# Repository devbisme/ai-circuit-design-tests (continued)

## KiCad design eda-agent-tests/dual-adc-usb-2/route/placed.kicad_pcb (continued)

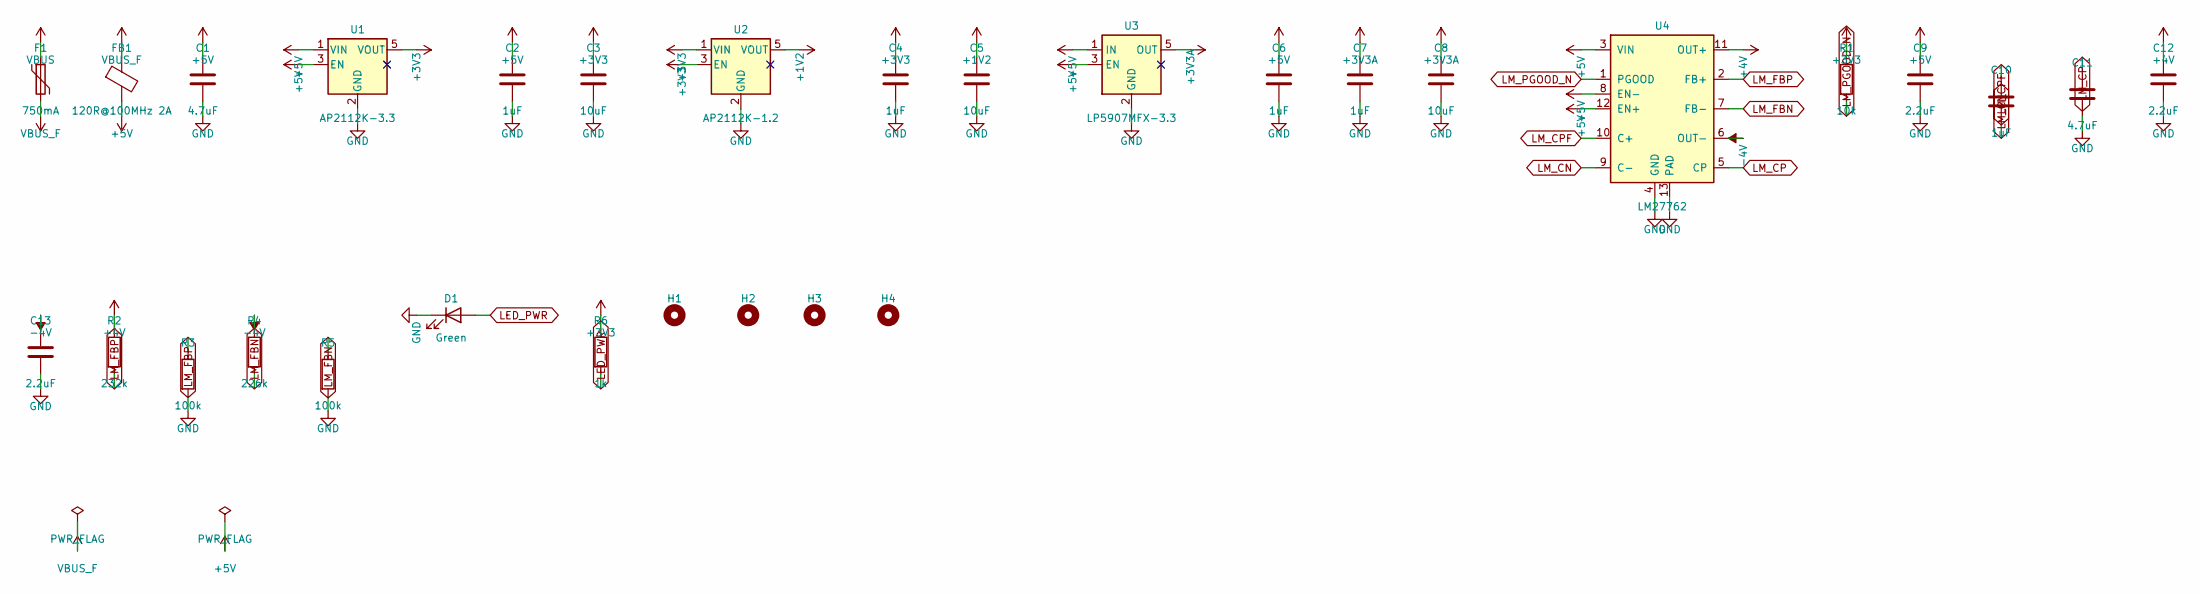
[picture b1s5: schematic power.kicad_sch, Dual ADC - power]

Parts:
C1, C11: 4.7uF; C_0805_2012Metric
C2, C4, C6, C7: 1uF; C_0603_1608Metric
C3, C5, C8: 10uF; C_0805_2012Metric
C9, C12, C13: 2.2uF; C_0805_2012Metric
C10: 1uF; C_0402_1005Metric
D1: Green; LED_0603_1608Metric
F1: 750mA; Fuse_1206_3216Metric; MPN 0ZCJ0050AF2E
FB1: 120R@100MHz 2A; L_0603_1608Metric; MPN BLM18AG601SN1D
H1, H2, H3, H4: MountingHole; MountingHole_3.2mm_M3
R1: 10k; R_0603_1608Metric
R2: 232k; R_0603_1608Metric
R3, R5: 100k; R_0603_1608Metric
R4: 226k; R_0603_1608Metric
R6: 1k; R_0603_1608Metric
U1: AP2112K-3.3; SOT-23-5; MPN AP2112K-3.3TRG1
U2: AP2112K-1.2; SOT-23-5; MPN AP2112K-1.2TRG1
U3: LP5907MFX-3.3; SOT-23-5; MPN LP5907MFX-3.3/NOPB
U4: LM27762; WSON-12-1EP_3x2mm_P0.5mm_EP1x2.65; MPN LM27762DSSR

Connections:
+1V2: C5.1, U2.5 (VOUT); also elsewhere on the board
+3V3A: C7.1, C8.1, U3.5 (OUT); also elsewhere on the board
+4V: C12.1, R2.1, U4.11 (OUT+); also elsewhere on the board
+5V: C1.1, C2.1, C6.1, C9.1, FB1.2, U1.1 (VIN), U1.3 (EN), U3.1 (IN), U3.3 (EN), U4.3 (VIN), U4.8 (EN-), U4.12 (EN+)
-4V: C13.1, R4.1, U4.6 (OUT-); also elsewhere on the board
LED_PWR: D1.2 (A), R6.2
LM_CN: C10.2, U4.9 (C-)
LM_CP: C11.1, U4.5 (CP)
LM_CPF: C10.1, U4.10 (C+)
LM_FBN: R4.2, R5.1, U4.7 (FB-)
LM_FBP: R2.2, R3.1, U4.2 (FB+)
LM_PGOOD_N: R1.2, U4.1 (PGOOD); also elsewhere on the board
VBUS: F1.1; also elsewhere on the board
VBUS_F: F1.2, FB1.1; also elsewhere on the board

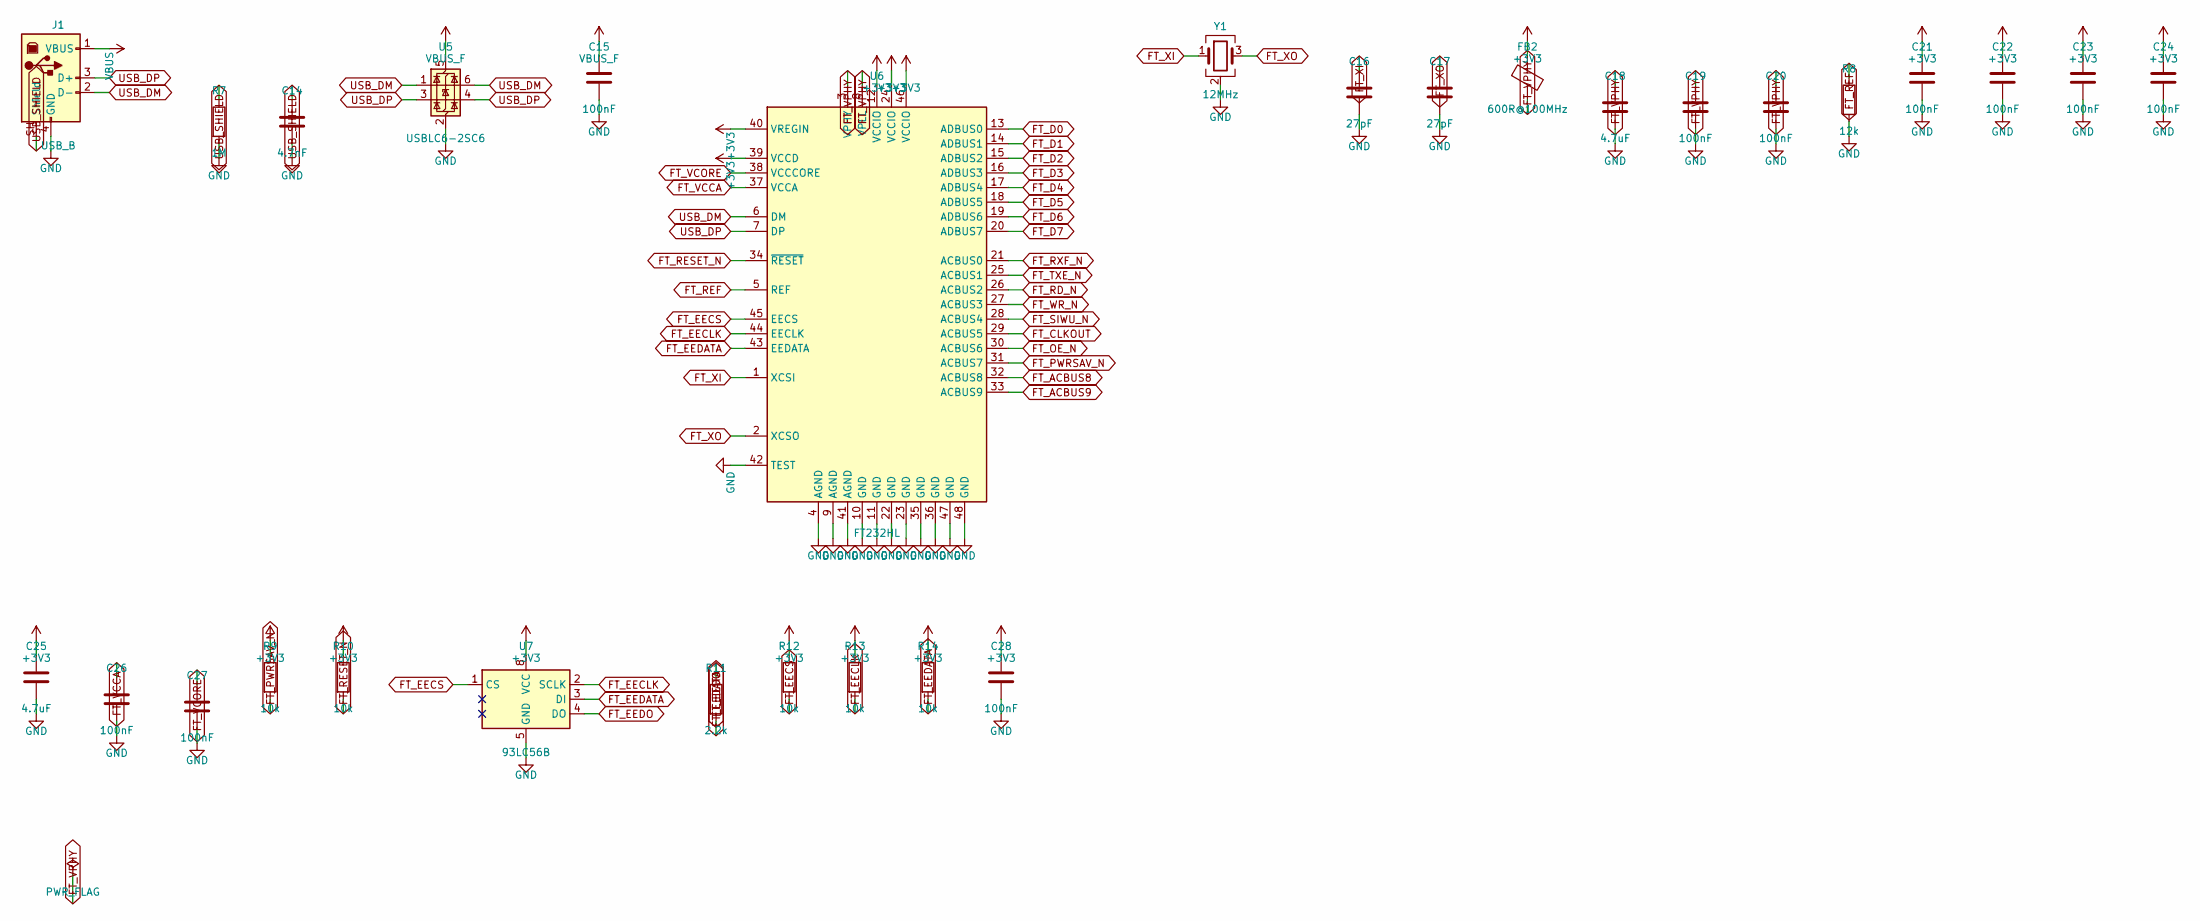
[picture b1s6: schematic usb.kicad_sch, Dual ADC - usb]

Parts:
C14: 4.7nF; C_0603_1608Metric
C15, C19, C20, C21, C22, C23, C24, C26, C27, C28: 100nF; C_0603_1608Metric
C16, C17: 27pF; C_0603_1608Metric
C18, C25: 4.7uF; C_0805_2012Metric
FB2: 600R@100MHz; L_0603_1608Metric; MPN BLM18AG601SN1D
J1: USB_B; USB_B_OST_USB-B1HSxx_Horizontal; MPN USB-B1HSW6
R7: 1M; R_0603_1608Metric
R8: 12k; R_0603_1608Metric; Tolerance 1%
R9, R10, R12, R13, R14: 10k; R_0603_1608Metric
R11: 2.2k; R_0603_1608Metric
U5: USBLC6-2SC6; SOT-23-6; MPN USBLC6-2SC6
U6: FT232HL; LQFP-48_7x7mm_P0.5mm; MPN FT232HL-REEL
U7: 93LC56B; SOIC-8_3.9x4.9mm_P1.27mm; MPN 93LC56BT-I/SN
Y1: 12MHz; Crystal_SMD_3225-4Pin_3.2x2.5mm; MPN ABM8-12.000MHZ-B2-T

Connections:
FT_ACBUS8: U6.32 (ACBUS8); also elsewhere on the board
FT_ACBUS9: U6.33 (ACBUS9); also elsewhere on the board
FT_CLKOUT: U6.29 (ACBUS5); also elsewhere on the board
FT_D0: U6.13 (ADBUS0); also elsewhere on the board
FT_D1: U6.14 (ADBUS1); also elsewhere on the board
FT_D2: U6.15 (ADBUS2); also elsewhere on the board
FT_D3: U6.16 (ADBUS3); also elsewhere on the board
FT_D4: U6.17 (ADBUS4); also elsewhere on the board
FT_D5: U6.18 (ADBUS5); also elsewhere on the board
FT_D6: U6.19 (ADBUS6); also elsewhere on the board
FT_D7: U6.20 (ADBUS7); also elsewhere on the board
FT_EECLK: R13.2, U6.44 (EECLK), U7.2 (SCLK)
FT_EECS: R12.2, U6.45 (EECS), U7.1 (CS)
FT_EEDATA: R11.2, R14.2, U6.43 (EEDATA), U7.3 (DI)
FT_EEDO: R11.1, U7.4 (DO)
FT_OE_N: U6.30 (ACBUS6); also elsewhere on the board
FT_PWRSAV_N: R9.2, U6.31 (ACBUS7)
FT_RD_N: U6.26 (ACBUS2); also elsewhere on the board
FT_REF: R8.1, U6.5 (REF)
FT_RESET_N: R10.2, U6.34 (~RESET)
FT_RXF_N: U6.21 (ACBUS0); also elsewhere on the board
FT_SIWU_N: U6.28 (ACBUS4); also elsewhere on the board
FT_TXE_N: U6.25 (ACBUS1); also elsewhere on the board
FT_VCCA: C26.1, U6.37 (VCCA)
FT_VCORE: C27.1, U6.38 (VCCCORE)
FT_VPHY: C18.1, C19.1, C20.1, FB2.2, U6.3 (VPHY), U6.8 (VPLL)
FT_WR_N: U6.27 (ACBUS3); also elsewhere on the board
FT_XI: C16.1, U6.1 (XCSI), Y1.1
FT_XO: C17.1, U6.2 (XCSO), Y1.3
USB_DM: J1.2 (D-), U5.1 (I/O1), U5.6 (I/O1), U6.6 (DM)
USB_DP: J1.3 (D+), U5.3 (I/O2), U5.4 (I/O2), U6.7 (DP)
USB_SHIELD: C14.1, J1.SH (Shield), R7.1
VBUS: J1.1 (VBUS); also elsewhere on the board
VBUS_F: C15.1, U5.5 (VBUS); also elsewhere on the board

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
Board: 4 copper layers, 179 parts (0 on the bottom side), 185 nets, no tracks yet.

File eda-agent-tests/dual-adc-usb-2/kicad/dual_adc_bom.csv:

"Refs","Value","Footprint","MPN","Manufacturer","Tolerance","Qty"
"C1,C11,C18,C25","4.7uF","Capacitor_SMD:C_0805_2012Metric","","","","4"
"C2,C4,C6,C7,C49,C50,C54,C55","1uF","Capacitor_SMD:C_0603_1608Metric","","","","8"
"C3,C5,C8,C61,C69,C80,C81,C83,C93","10uF","Capacitor_SMD:C_0805_2012Metric","","","","9"
"C9,C12,C13,C48,C51,C53,C56","2.2uF","Capacitor_SMD:C_0805_2012Metric","","","","7"
"C10","1uF","Capacitor_SMD:C_0402_1005Metric","","","","1"
"C14","4.7nF","Capacitor_SMD:C_0603_1608Metric","","","","1"
"C15,C19-C24,C26-C30,C36,C37,C44,C45,C47,C52,C57-C60,C62-C68,C70-C79,C82,C84-C92","100nF","Capacitor_SMD:C_0603_1608Metric","","","","49"
"C16,C17","27pF","Capacitor_SMD:C_0603_1608Metric","","","","2"
"C31,C39","12pF","Capacitor_SMD:C_0603_1608Metric","","","","2"
"C32,C40","2.7pF","Capacitor_SMD:C_0603_1608Metric","","","","2"
"C33,C41","22pF","Capacitor_SMD:C_0603_1608Metric","","","","2"
"C34,C35,C42,C43","33pF","Capacitor_SMD:C_0603_1608Metric","","","","4"
"C38,C46","100pF","Capacitor_SMD:C_0603_1608Metric","","","","2"
"D1","Green","LED_SMD:LED_0603_1608Metric","","","","1"
"D2,D3","BAV99","Package_TO_SOT_SMD:SOT-23","BAV99,215","Nexperia","","2"
"D4,D5","Yellow","LED_SMD:LED_0603_1608Metric","","","","2"
"F1","750mA","Fuse:Fuse_1206_3216Metric","0ZCJ0050AF2E","Bel Fuse","","1"
"FB1","120R@100MHz 2A","Inductor_SMD:L_0603_1608Metric","BLM18AG601SN1D","Murata","","1"
"FB2,FB3","600R@100MHz","Inductor_SMD:L_0603_1608Metric","BLM18AG601SN1D","Murata","","2"
"J1","USB_B","Connector_USB:USB_B_OST_USB-B1HSxx_Horizontal","USB-B1HSW6","On Shore Technology","","1"
"J2","BNC_A","Connector_Coaxial:BNC_Amphenol_B6252HB-NPP3G-50_Horizontal","B6252HB-NPP3G-50","Amphenol RF","","1"
"J3","BNC_B","Connector_Coaxial:BNC_Amphenol_B6252HB-NPP3G-50_Horizontal","B6252HB-NPP3G-50","Amphenol RF","","1"
"J4","PROG","Connector_PinHeader_2.54mm:PinHeader_2x04_P2.54mm_Vertical","","","","1"
"R1,R9,R10,R12-R14,R33,R40-R44","10k","Resistor_SMD:R_0603_1608Metric","","","","12"
"R2","232k","Resistor_SMD:R_0603_1608Metric","","","","1"
"R3,R5","100k","Resistor_SMD:R_0603_1608Metric","","","","2"
"R4","226k","Resistor_SMD:R_0603_1608Metric","","","","1"
"R6,R17-R21,R26-R30,R45,R46","1k","Resistor_SMD:R_0603_1608Metric","","","","13"
"R7","1M","Resistor_SMD:R_0603_1608Metric","","","","1"
"R8","12k","Resistor_SMD:R_0603_1608Metric","","","1%","1"
"R11","2.2k","Resistor_SMD:R_0603_1608Metric","","","","1"
"R15,R24","909k","Resistor_SMD:R_0603_1608Metric","","","0.1%","2"
"R16,R25","90.9k","Resistor_SMD:R_0603_1608Metric","","","0.1%","2"
"R22,R23,R31,R32","49.9","Resistor_SMD:R_0603_1608Metric","","","","4"
"R34","20k","Resistor_SMD:R_0603_1608Metric","","","","1"
"R35-R37","33","Resistor_SMD:R_0603_1608Metric","","","","3"
"R38,R39","100","Resistor_SMD:R_0603_1608Metric","","","","2"
"RN1-RN7","33","Resistor_SMD:R_Array_Convex_4x0603","CAY16-330J4LF","Bourns","","7"
"U1","AP2112K-3.3","Package_TO_SOT_SMD:SOT-23-5","AP2112K-3.3TRG1","Diodes Inc","","1"
"U2","AP2112K-1.2","Package_TO_SOT_SMD:SOT-23-5","AP2112K-1.2TRG1","Diodes Inc","","1"
"U3","LP5907MFX-3.3","Package_TO_SOT_SMD:SOT-23-5","LP5907MFX-3.3/NOPB","Texas Instruments","","1"
"U4","LM27762","Package_SON:WSON-12-1EP_3x2mm_P0.5mm_EP1x2.65","LM27762DSSR","Texas Instruments","","1"
"U5","USBLC6-2SC6","Package_TO_SOT_SMD:SOT-23-6","USBLC6-2SC6","STMicroelectronics","","1"
"U6","FT232HL","Package_QFP:LQFP-48_7x7mm_P0.5mm","FT232HL-REEL","FTDI","","1"
"U7","93LC56B","Package_SO:SOIC-8_3.9x4.9mm_P1.27mm","93LC56BT-I/SN","Microchip","","1"
"U8","OPA1656ID","Package_SO:SOIC-8_3.9x4.9mm_P1.27mm","OPA1656IDR","Texas Instruments","","1"
"U9,U10","THS4521ID","Package_SO:SOIC-8_3.9x4.9mm_P1.27mm","THS4521IDR","Texas Instruments","","2"
"U11","LTC2290CUP","Package_DFN_QFN:QFN-64-1EP_9x9mm_P0.5mm_EP7.15x7.15mm","LTC2290CUP#PBF","Analog Devices","","1"
"U12","ICE40HX4K-TQ144","Package_QFP:TQFP-144_20x20mm_P0.5mm","ICE40HX4K-TQ144","Lattice","","1"
"U13","W25Q32JVSS","Package_SO:SOIC-8_5.3x5.3mm_P1.27mm","W25Q32JVSSIQ","Winbond","","1"
"U14","MT48LC16M16A2TG-6A","Package_SO:TSOP-II-54_22.2x10.16mm_P0.8mm","MT48LC16M16A2P-6A:G","Micron","","1"
"X1","ASE-10.000MHz","Oscillator:Oscillator_SMD_Abracon_ASE-4Pin_3.2x2.5mm","ASE-10.000MHZ-LC-T","Abracon","","1"
"Y1","12MHz","Crystal:Crystal_SMD_3225-4Pin_3.2x2.5mm","ABM8-12.000MHZ-B2-T","Abracon","","1"

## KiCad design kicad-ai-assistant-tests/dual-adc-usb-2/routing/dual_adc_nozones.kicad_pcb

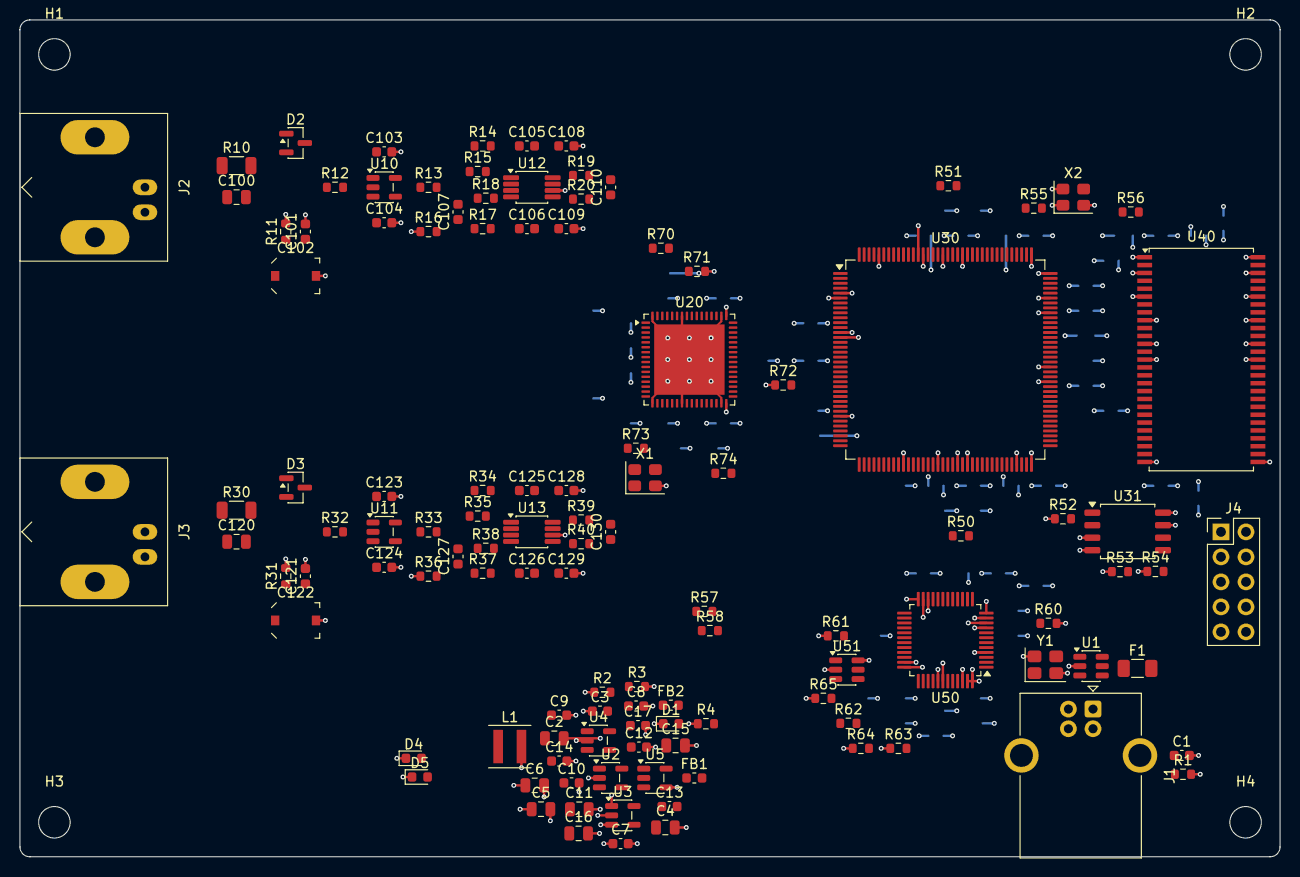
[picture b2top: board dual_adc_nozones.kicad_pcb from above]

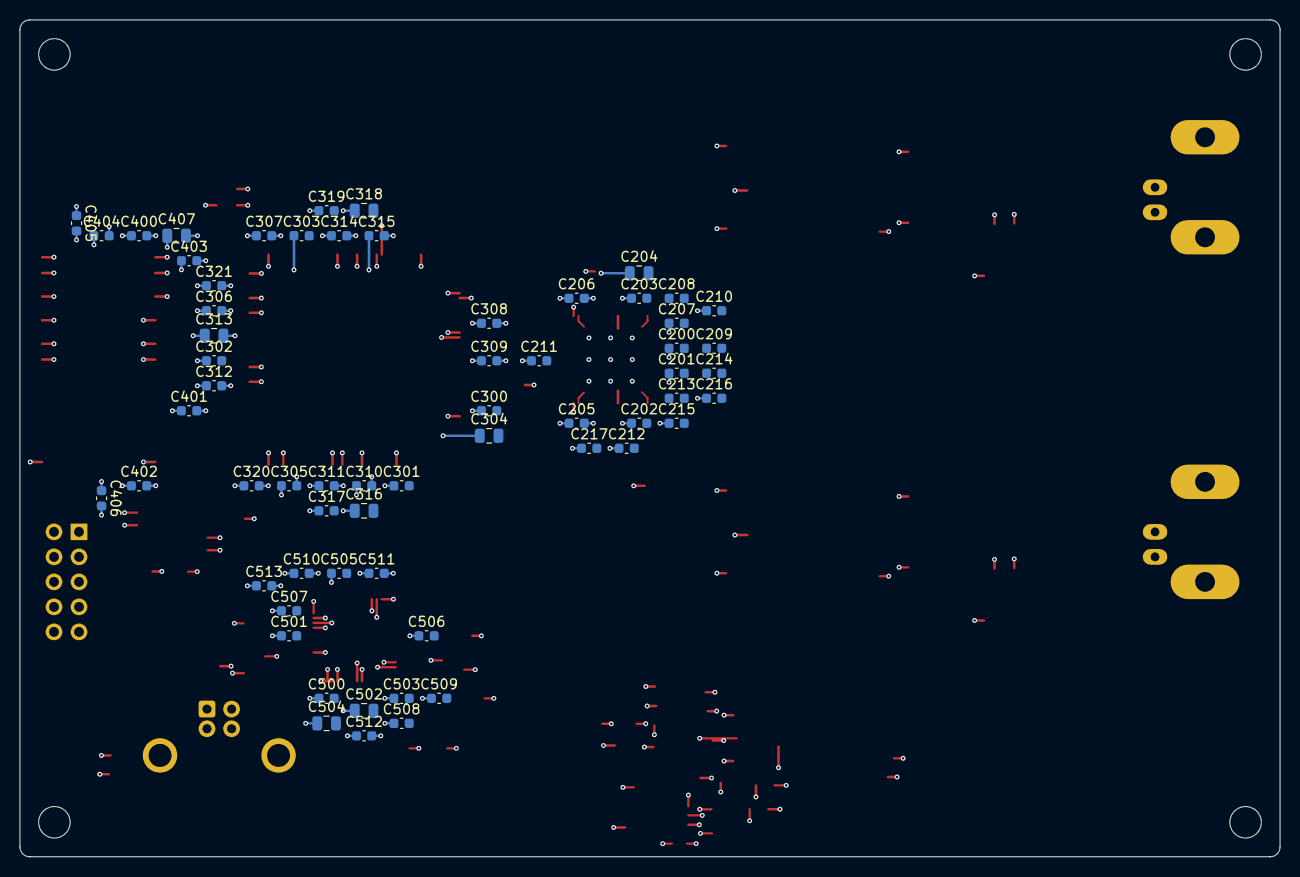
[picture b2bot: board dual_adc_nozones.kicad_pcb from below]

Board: 4 copper layers, 128.0 x 85.0 mm, 182 parts (62 on the bottom side), 160 nets.

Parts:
C1: 4.7n; C_0603_1608Metric
C2, C4, C15, C16, C502, C504: 4.7u; C_0805_2012Metric
C3: 22p; C_0603_1608Metric
C5, C6: 22u; C_0805_2012Metric
C7, C8, C9, C10, C13, C14: 1u; C_0603_1608Metric
C11, C204, C304, C313, C316, C318, C407: 10u; C_0805_2012Metric
C12, C17, C103, C104, C108, C109, C123, C124, C128, C129, C200, C201, C202, C203, C205, C206, C209, C210, C211, C214, C215, C216, C217, C300, C301, C302, C303, C305, C306, C307, C308, C309, C310, C311, C312, C314, C315, C317, C319, C320, C321, C400, C401, C402, C403, C404, C405, C406, C503, C505, C506, C507, C508, C509, C510, C511, C512, C513: 100n; C_0603_1608Metric
C100, C120: 15p C0G 100V; C_0805_2012Metric
C101, C121: 120p C0G; C_0603_1608Metric
C102, C122: 5-30p; C_Trimmer_Murata_TZC3
C105, C106, C125, C126: 47p C0G; C_0603_1608Metric
C107, C127: 220p C0G; C_0603_1608Metric
C110, C130: 470p C0G; C_0603_1608Metric
C207, C208, C212, C213: 2.2u; C_0603_1608Metric
C500, C501: 18p; C_0603_1608Metric
D1, D4: green; LED_0603_1608Metric
D2, D3: BAV99; SOT-23
D5: yellow; LED_0603_1608Metric
F1: 0.5A hold; Fuse_1206_3216Metric
FB1, FB2: BLM18PG221; L_0603_1608Metric
H1, H2, H3, H4: M3; MountingHole_3.2mm_M3
J1: USB-B; USB_B_OST_USB-B1HSxx_Horizontal
J2, J3: BNC; BNC_Amphenol_B6252HB-NPP3G-50_Horizontal
J4: PROG; PinHeader_2x05_P2.54mm_Vertical
L1: 2.2u XFL4020-222; L_Coilcraft_XxL4020
R1: 1M; R_0603_1608Metric
R2: 453k; R_0603_1608Metric
R3: 100k; R_0603_1608Metric
R4, R12, R32, R57, R58: 1k; R_0603_1608Metric
R10, R30: 909k 0.1%; R_1206_3216Metric
R11, R31: 100k 0.1%; R_0603_1608Metric
R13, R16, R33, R36: 806; R_0603_1608Metric
R14, R17, R34, R37: 768; R_0603_1608Metric
R15, R18, R35, R38: 147; R_0603_1608Metric
R19, R20, R39, R40: 49.9; R_0603_1608Metric
R50, R51: 100; R_0603_1608Metric
R52, R53, R54, R61, R63, R64, R65, R71, R72: 10k; R_0603_1608Metric
R55, R73, R74: 33; R_0603_1608Metric
R56: 22; R_0603_1608Metric
R60: 12k 1%; R_0603_1608Metric
R62: 2.2k; R_0603_1608Metric
R70: 20k; R_0603_1608Metric
U1: USBLC6-2SC6; SOT-23-6
U2: TLV62569DBV; SOT-23-5
U3: TLV73312PDBV; SOT-23-5
U4: LP5907MFX-3.3; SOT-23-5
U5: TPS60403DBV; SOT-23-5
U10, U11: OPA810IDBVR; SOT-23-5
U12, U13: THS4521IDGK; VSSOP-8_3x3mm_P0.65mm
U20: LTC2290CUP; QFN-64-1EP_9x9mm_P0.5mm_EP7.15x7.15mm
U30: ICE40HX4K-TQ144; TQFP-144_20x20mm_P0.5mm
U31: W25Q32JVSSIQ; SOIC-8_5.3x5.3mm_P1.27mm
U40: MT48LC16M16A2P-6A; TSOP-II-54_22.2x10.16mm_P0.8mm
U50: FT232HL; LQFP-48_7x7mm_P0.5mm
U51: 93LC56BT-I/OT; SOT-23-6
X1: ASE-10.000MHZ; Oscillator_SMD_Abracon_ASE-4Pin_3.2x2.5mm
X2: ASE-50.000MHZ; Oscillator_SMD_Abracon_ASE-4Pin_3.2x2.5mm
Y1: 12MHz 10pF; Crystal_SMD_3225-4Pin_3.2x2.5mm

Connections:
+1V2: C8.1, C300.1, C301.1, C302.1, C303.1, C304.1, R50.1, R51.1, U3.5 (OUT), U30.27 (VCC), U30.40 (VCC), U30.92 (VCC), U30.111 (VCC)
+3.3VA: C10.1, C200.1, C201.1, C202.1, C203.1, C204.1, C217.1, R70.1, U4.5 (OUT), U20.7 (VDD), U20.10 (VDD), U20.18 (VDD), U20.19 (SENSEB), U20.21 (MUX), U20.62 (SENSEA), U20.63 (VDD), X1.1 (EN), X1.4 (Vdd)
+3V3: C3.1, C5.1, C6.1, C7.1, C205.1, C206.1, C305.1, C306.1, C307.1, C308.1, C309.1, C310.1, C311.1, C312.1, C313.1, C314.1, C315.1, C320.1, C321.1, C400.1, C401.1, C402.1, C403.1, C404.1, C405.1, C406.1, C407.1, C510.1, C511.1, C512.1, C513.1, J4.1, L1.2, R2.1, R4.1, R52.1, R53.1, R54.1, R61.1, R63.1, R64.1, R65.1, R72.1, U3.1 (IN), U3.3 (EN), U20.32 (OVDD), U20.49 (OVDD), U30.6 (VCCIO_3), U30.30 (VCCIO_3), U30.46 (VCCIO_2), U30.57 (VCCIO_2), U30.72 (VCC_SPI), U30.89 (VCCIO_1), U30.100 (VCCIO_1), U30.108 (VPP_2V5), U30.109 (VPP_FAST), U30.123 (VCCIO_0), U30.131 (VCCIO_0), U31.3 (~WP/IO_{2}), U31.7 (~HOLD/~RESET/IO_{3}), U31.8 (VCC), U40.1 (VDD), U40.3 (VDDQ), U40.9 (VDDQ), U40.14 (VDD), U40.27 (VDD), U40.43 (VDDQ), U40.49 (VDDQ), U50.12 (VCCIO), U50.24 (VCCIO), U50.46 (VCCIO), U51.6 (VCC), X2.1 (EN), X2.4 (Vdd)
+5V: C2.1, C4.1, C9.1, C14.1, C502.1, C503.1, F1.2, FB1.1, U2.1 (EN), U2.4 (VIN), U4.1 (IN), U4.3 (EN), U5.2 (IN), U50.40 (VREGIN)
+5VA: C11.1, C12.1, C103.1, C108.1, C123.1, C128.1, D2.2 (A), D3.2 (A), FB1.2, U10.5 (V+), U11.5 (V+), U12.3 (V_{S+}), U12.7 (~PD), U13.3 (V_{S+}), U13.7 (~PD)
-5V: C15.1, FB2.1, U5.1 (OUT)
-5VA: C16.1, C17.1, C104.1, C124.1, D2.1 (K), D3.1 (K), FB2.2, U10.2 (V-), U11.2 (V-)
/Analog front ends (A, B)/ATTA: C100.2, C101.1, C102.1, D2.3 (K), R10.2, R11.1, R12.1
/Analog front ends (A, B)/ATTB: C120.2, C121.1, C122.1, D3.3 (K), R30.2, R31.1, R32.1
/Analog front ends (A, B)/BUFA: R13.1, U10.1, U10.4 (-)
/Analog front ends (A, B)/BUFB: R33.1, U11.1, U11.4 (-)
/Analog front ends (A, B)/BUFINA: R12.2, U10.3 (+)
/Analog front ends (A, B)/BUFINB: R32.2, U11.3 (+)
/Analog front ends (A, B)/FDAINNA: C105.2, R15.2, U12.1 (-)
/Analog front ends (A, B)/FDAINNB: C125.2, R35.2, U13.1 (-)
/Analog front ends (A, B)/FDAINPA: C106.2, R18.2, U12.8 (+)
/Analog front ends (A, B)/FDAINPB: C126.2, R38.2, U13.8 (+)
/Analog front ends (A, B)/FDAONA: C106.1, R17.2, R19.1, U12.5
/Analog front ends (A, B)/FDAONB: C126.1, R37.2, R39.1, U13.5
/Analog front ends (A, B)/FDAOPA: C105.1, R14.2, R20.1, U12.4
/Analog front ends (A, B)/FDAOPB: C125.1, R34.2, R40.1, U13.4
/Analog front ends (A, B)/INA: C100.1, J2.1 (In), R10.1
/Analog front ends (A, B)/INB: C120.1, J3.1 (In), R30.1
/Analog front ends (A, B)/MFBNA: C107.2, R16.2, R17.1, R18.1
/Analog front ends (A, B)/MFBNB: C127.2, R36.2, R37.1, R38.1
/Analog front ends (A, B)/MFBPA: C107.1, R13.2, R14.1, R15.1
/Analog front ends (A, B)/MFBPB: C127.1, R33.2, R34.1, R35.1
/FT232H USB 2.0 bridge/FT_EECLK: R64.2, U50.44 (EECLK), U51.4 (CLK)
/FT232H USB 2.0 bridge/FT_EECS: R63.2, U50.45 (EECS), U51.5 (CS)
/FT232H USB 2.0 bridge/FT_EEDATA: R62.2, R65.2, U50.43 (EEDATA), U51.3 (DI)
/FT232H USB 2.0 bridge/FT_EEDO: R62.1, U51.1 (DO)
/FT232H USB 2.0 bridge/FT_REF: R60.1, U50.5 (REF)
/FT232H USB 2.0 bridge/FT_RESETn: R61.2, U50.34 (~RESET)
/FT232H USB 2.0 bridge/FT_VCCA: C509.1, U50.37 (VCCA)
/FT232H USB 2.0 bridge/FT_VCCD: C504.1, C505.1, C506.1, C507.1, U50.3 (VPHY), U50.8 (VPLL), U50.39 (VCCD)
/FT232H USB 2.0 bridge/FT_VCORE: C508.1, U50.38 (VCCCORE)
/FT232H USB 2.0 bridge/FT_XI: C500.1, U50.1 (XCSI), Y1.1
/FT232H USB 2.0 bridge/FT_XO: C501.1, U50.2 (XCSO), Y1.3
/LTC2290 ADC and sample clock/ADC_CLK: R73.2, U20.8 (CLKA), U20.9 (CLKB)
/LTC2290 ADC and sample clock/ADC_MODE: R70.2, R71.1, U20.60 (MODE)
/LTC2290 ADC and sample clock/OSC10M: R73.1, R74.1, X1.3 (OUT)
/LTC2290 ADC and sample clock/REFHA: C208.1, C209.1, C210.1, U20.3 (REFHA), U20.4 (REFHA)
/LTC2290 ADC and sample clock/REFHB: C213.1, C214.1, C215.1, U20.13 (REFHB), U20.14 (REFHB)
/LTC2290 ADC and sample clock/REFLA: C208.2, C209.2, C211.1, U20.5 (REFLA), U20.6 (REFLA)
/LTC2290 ADC and sample clock/REFLB: C213.2, C214.2, C216.1, U20.11 (REFLB), U20.12 (REFLB)
/USB input and power/BUCK_FB: C3.2, R2.2, R3.1, U2.5 (FB)
/USB input and power/BUCK_SW: L1.1, U2.3 (SW)
/USB input and power/CP_FLYN: C13.2, U5.3 (C_{FLY-})
/USB input and power/CP_FLYP: C13.1, U5.5 (C_{FLY+})
/USB input and power/LED_PWR_A: D1.2 (A), R4.2
/USB input and power/USB_SHIELD: C1.1, J1.SH (Shield), R1.1
/iCE40 FPGA, config, clocks/FLASH_CSn: J4.4, R52.2, U30.71 (IOB_108_SS), U31.1 (~CS)
/iCE40 FPGA, config, clocks/FLASH_MISO: J4.6, U30.68 (IOB_106_SDI), U31.2 (DO/IO_{1})
/iCE40 FPGA, config, clocks/FLASH_MOSI: J4.5, U30.67 (IOB_105_SDO), U31.5 (DI/IO_{0})
/iCE40 FPGA, config, clocks/FLASH_SCK: J4.3, U30.70 (IOB_107_SCK), U31.6 (CLK)
/iCE40 FPGA, config, clocks/FPGA_CDONE: J4.8, R54.2, U30.65 (CDONE)
/iCE40 FPGA, config, clocks/FPGA_CRESETn: J4.7, R53.2, U30.66 (~CRESET)
/iCE40 FPGA, config, clocks/LED1_A: D4.2 (A), R57.2
/iCE40 FPGA, config, clocks/LED2_A: D5.2 (A), R58.2
/iCE40 FPGA, config, clocks/LED_D1: R57.1, U30.63 (IOB_103_CBSEL0)
/iCE40 FPGA, config, clocks/LED_D2: R58.1, U30.64 (IOB_104_CBSEL1)
/iCE40 FPGA, config, clocks/OSC50M: R55.1, X2.3 (OUT)
/iCE40 FPGA, config, clocks/SD_CLK_SRC: R56.1, U30.93 (IOR_140_GBIN3)
/iCE40 FPGA, config, clocks/SYS_CLK: R55.2, U30.94 (IOR_141_GBIN2)
/iCE40 FPGA, config, clocks/VCCPLL0: C316.1, C317.1, R50.2, U30.54 (VCCPLL0)
/iCE40 FPGA, config, clocks/VCCPLL1: C318.1, C319.1, R51.2, U30.126 (VCCPLL1)
ADC_CLK_FPGA: R74.2, U30.21 (IOL_14A_GBIN6)
ADC_DA0: U20.43 (DA0), U30.17 (IOL_12A)
ADC_DA1: U20.44 (DA1), U30.16 (IOL_10B)
ADC_DA2: U20.45 (DA2), U30.15 (IOL_10A)
ADC_DA3: U20.46 (DA3), U30.12 (IOL_8B)
ADC_DA4: U20.47 (DA4), U30.11 (IOL_8A)
ADC_DA5: U20.48 (DA5), U30.10 (IOL_5B)
ADC_DA6: U20.51 (DA6), U30.9 (IOL_5A)
ADC_DA7: U20.52 (DA7), U30.8 (IOL_4B)
ADC_DA8: U20.53 (DA8), U30.7 (IOL_4A)
ADC_DA9: U20.54 (DA9), U30.4 (IOL_3B)
ADC_DA10: U20.55 (DA10), U30.3 (IOL_3A)
ADC_DA11: U20.56 (DA11), U30.2 (IOL_2B)
ADC_DB0: U20.26 (DB0), U30.33 (IOL_25A)
ADC_DB1: U20.27 (DB1), U30.32 (IOL_24B)
ADC_DB2: U20.28 (DB2), U30.31 (IOL_24A)
ADC_DB3: U20.29 (DB3), U30.29 (IOL_23B)
ADC_DB4: U20.30 (DB4), U30.28 (IOL_23A)
ADC_DB5: U20.33 (DB5), U30.26 (IOL_18B)
ADC_DB6: U20.34 (DB6), U30.25 (IOL_18A)
ADC_DB7: U20.35 (DB7), U30.24 (IOL_17B)
ADC_DB8: U20.36 (DB8), U30.23 (IOL_17A)
ADC_DB9: U20.37 (DB9), U30.22 (IOL_14B)
ADC_DB10: U20.38 (DB10), U30.20 (IOL_13B_GBIN7)
ADC_DB11: U20.39 (DB11), U30.19 (IOL_13A)
ADC_OFA: U20.57 (OFA), U30.1 (IOL_2A)
ADC_OFB: U20.40 (OFB), U30.18 (IOL_12B)
ADC_SHDN: R72.2, U20.22 (SHDNB), U20.59 (SHDNA), U30.34 (IOL_25B)
AINA_N: C110.2, R20.2, U20.2 (AINA-)
AINA_P: C110.1, R19.2, U20.1 (AINA+)
AINB_N: C130.2, R40.2, U20.15 (AINB-)
AINB_P: C130.1, R39.2, U20.16 (AINB+)
FT_AC8: U30.62 (IOB_102), U50.32 (ACBUS8)
FT_CLKOUT: U30.52 (IOB_82_GBIN4), U50.29 (ACBUS5)
FT_D0: U30.37 (IOB_56), U50.13 (ADBUS0)
FT_D1: U30.38 (IOB_57), U50.14 (ADBUS1)
FT_D2: U30.39 (IOB_61), U50.15 (ADBUS2)
FT_D3: U30.41 (IOB_63), U50.16 (ADBUS3)
FT_D4: U30.42 (IOB_64), U50.17 (ADBUS4)
FT_D5: U30.43 (IOB_71), U50.18 (ADBUS5)
FT_D6: U30.44 (IOB_72), U50.19 (ADBUS6)
FT_D7: U30.45 (IOB_73), U50.20 (ADBUS7)
FT_OEn: U30.56 (IOB_94), U50.30 (ACBUS6)
FT_PWRENn: U30.61 (IOB_96), U50.33 (ACBUS9)
FT_RDn: U30.49 (IOB_81_GBIN5), U50.26 (ACBUS2)
FT_RXFn: U30.47 (IOB_79), U50.21 (ACBUS0)
FT_SIWUn: U30.60 (IOB_95), U50.28 (ACBUS4)
FT_TXEn: U30.48 (IOB_80), U50.25 (ACBUS1)
FT_WRn: U30.55 (IOB_91), U50.27 (ACBUS3)
GND: C1.2, C2.2, C4.2, C5.2, C6.2, C7.2, C8.2, C9.2, C10.2, C11.2, C12.2, C14.2, C15.2, C16.2, C17.2, C101.2, C102.2, C103.2, C104.2, C108.2, C109.2, C121.2, C122.2, C123.2, C124.2, C128.2, C129.2, C200.2, C201.2, C202.2, C203.2, C204.2, C205.2, C206.2, C207.2, C210.2, C211.2, C212.2, C215.2, C216.2, C217.2, C300.2, C301.2, C302.2, C303.2, C304.2, C305.2, C306.2, C307.2, C308.2, C309.2, C310.2, C311.2, C312.2, C313.2, C314.2, C315.2, C316.2, C317.2, C318.2, C319.2, C320.2, C321.2, C400.2, C401.2, C402.2, C403.2, C404.2, C405.2, C406.2, C407.2, C500.2, C501.2, C502.2, C503.2, C504.2, C505.2, C506.2, C507.2, C508.2, C509.2, C510.2, C511.2, C512.2, C513.2, D1.1 (K), D4.1 (K), D5.1 (K), J1.4 (GND), J2.2 (Ext), J3.2 (Ext), J4.2, J4.9, J4.10, R1.2, R3.2, R11.2, R16.1, R31.2, R36.1, R60.2, R71.2, U1.2 (GND), U2.2 (GND), U3.2 (GND), U4.2 (GND), U5.4 (GND), U12.6 (V_{S-}), U13.6 (V_{S-}), U20.17 (GND), U20.23 (~OEB), U20.31 (OGND), U20.50 (OGND), U20.58 (~OEA), U20.64 (GND), U20.65 (GND), U30.5 (GND), U30.13 (GND), U30.14 (GND), U30.53 (GNDPLL0), U30.59 (GND), U30.69 (GND), U30.86 (GND), U30.103 (GND), U30.127 (GNDPLL1), U30.132 (GND), U30.140 (GND), U31.4 (GND), U40.6 (VSSQ), U40.12 (VSSQ), U40.28 (VSS), U40.41 (VSS), U40.46 (VSSQ), U40.52 (VSSQ), U40.54 (VSS), U50.4 (AGND), U50.9 (AGND), U50.10 (GND), U50.11 (GND), U50.22 (GND), U50.23 (GND), U50.35 (GND), U50.36 (GND), U50.41 (AGND), U50.42 (TEST), U50.47 (GND), U50.48 (GND), U51.2 (GND), X1.2 (GND), X2.2 (GND), Y1.2 (G), Y1.4 (G)
SD_A0: U30.110 (IOT_168), U40.23 (A0)
SD_A1: U30.112 (IOT_169), U40.24 (A1)
SD_A2: U30.113 (IOT_170), U40.25 (A2)
SD_A3: U30.114 (IOT_171), U40.26 (A3)
SD_A4: U30.115 (IOT_172), U40.29 (A4)
SD_A5: U30.116 (IOT_173), U40.30 (A5)
SD_A6: U30.117 (IOT_174), U40.31 (A6)
SD_A7: U30.118 (IOT_177), U40.32 (A7)
SD_A8: U30.119 (IOT_178), U40.33 (A8)
SD_A9: U30.120 (IOT_179), U40.34 (A9)
SD_A10: U30.121 (IOT_181), U40.22 (A10)
SD_A11: U30.122 (IOT_190), U40.35 (A11)
SD_A12: U30.124 (IOT_191), U40.36 (A12)
SD_BA0: U30.88 (IOR_137), U40.20 (BA0)
SD_BA1: U30.90 (IOR_138), U40.21 (BA1)
SD_CASn: U30.84 (IOR_120), U40.17 (~CAS)
SD_CKE: U30.91 (IOR_139), U40.37 (CKE)
SD_CLK: R56.2, U40.38 (CLK)
SD_CSn: U30.87 (IOR_136), U40.19 (~CS)
SD_DQ0: U30.73 (IOR_109), U40.2 (DQ0)
SD_DQ1: U30.74 (IOR_110), U40.4 (DQ1)
SD_DQ2: U30.75 (IOR_111), U40.5 (DQ2)
SD_DQ3: U30.76 (IOR_112), U40.7 (DQ3)
SD_DQ4: U30.78 (IOR_114), U40.8 (DQ4)
SD_DQ5: U30.79 (IOR_115), U40.10 (DQ5)
SD_DQ6: U30.80 (IOR_116), U40.11 (DQ6)
SD_DQ7: U30.81 (IOR_117), U40.13 (DQ7)
SD_DQ8: U30.96 (IOR_146), U40.42 (DQ8)
SD_DQ9: U30.97 (IOR_147), U40.44 (DQ9)
SD_DQ10: U30.98 (IOR_148), U40.45 (DQ10)
SD_DQ11: U30.99 (IOR_152), U40.47 (DQ11)
SD_DQ12: U30.101 (IOR_160), U40.48 (DQ12)
SD_DQ13: U30.102 (IOR_161), U40.50 (DQ13)
SD_DQ14: U30.104 (IOR_164), U40.51 (DQ14)
SD_DQ15: U30.105 (IOR_165), U40.53 (DQ15)
SD_DQMH: U30.95 (IOR_144), U40.39 (DQMH)
SD_DQML: U30.82 (IOR_118), U40.15 (DQML)
SD_RASn: U30.85 (IOR_128), U40.18 (~RAS)
SD_WEn: U30.83 (IOR_119), U40.16 (~WE)
USB_DM: J1.2 (D-), U1.1 (I/O1), U1.6 (I/O1), U50.6 (DM)
USB_DP: J1.3 (D+), U1.3 (I/O2), U1.4 (I/O2), U50.7 (DP)
VBUS: F1.1, J1.1 (VBUS), U1.5 (VBUS)
VCMA: C109.1, C207.1, U12.2 (V_{OCM}), U20.61 (VCMA)
VCMB: C129.1, C212.1, U13.2 (V_{OCM}), U20.20 (VCMB)

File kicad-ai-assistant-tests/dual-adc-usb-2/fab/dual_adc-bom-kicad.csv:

"Reference","Value","Footprint","QUANTITY","Description"
"C1","4.7n","Capacitor_SMD:C_0603_1608Metric","1","shield RF tie (250 V)"
"C2,C4,C15,C16,C502,C504","4.7u","Capacitor_SMD:C_0805_2012Metric","6","+5V bulk (keep total VBUS C ~10 uF),Unpolarized capacitor,VCCD 3.3 V out,VREGIN,buck input,charge-pump output"
"C3","22p","Capacitor_SMD:C_0603_1608Metric","1","FB feed-forward"
"C5,C6","22u","Capacitor_SMD:C_0805_2012Metric","2","buck output"
"C7-C10,C13,C14","1u","Capacitor_SMD:C_0603_1608Metric","6","LDO in,LDO out,charge-pump input,flying cap"
"C11,C204,C304,C313,C316,C318,C407","10u","Capacitor_SMD:C_0805_2012Metric","7","ADC VDD,FPGA VCC,FPGA VCCIO,PLL filter,SDRAM VDD/VDDQ,Unpolarized capacitor"
"C12,C17,C103,C104,C108,C109,C123,C124,C128,C129,C200-C203,C205,C206,C209-C211,C214-C217,C300-C303,C305-C312,C314,C315,C317,C319-C321,C400-C406,C503,C505-C513","100n","Capacitor_SMD:C_0603_1608Metric","58","ADC OVDD,ADC VDD,EEPROM bypass,FPGA VCC,FPGA VCCIO,FPGA VCC_SPI / VPP,FT232H VCCIO,PLL filter,REFH bypass,REFH-REFL bypass,REFL bypass,SDRAM VDD/VDDQ,Unpolarized capacitor,VCCA 1.8 V out,VCCCORE 1.8 V out,VCCD,VOCM local bypass,VPHY,VPLL,VREGIN,flash bypass,oscillator bypass"
"C100,C120","15p C0G 100V","Capacitor_SMD:C_0805_2012Metric","2","attenuator top comp"
"C101,C121","120p C0G","Capacitor_SMD:C_0603_1608Metric","2","attenuator bottom comp"
"C102,C122","5-30p","Capacitor_SMD:C_Trimmer_Murata_TZC3","2","compensation trim (adjust for flat 1 kHz square wave)"
"C105,C106,C125,C126","47p C0G","Capacitor_SMD:C_0603_1608Metric","4","MFB C2 (reference leg),MFB C2 (signal leg)"
"C107,C127","220p C0G","Capacitor_SMD:C_0603_1608Metric","2","MFB C1 (differential)"
"C110,C130","470p C0G","Capacitor_SMD:C_0603_1608Metric","2","differential RC pole, ~3.4 MHz"
"C207,C208,C212,C213","2.2u","Capacitor_SMD:C_0603_1608Metric","4","REFH-REFL bypass,VCM bypass"
"C500,C501","18p","Capacitor_SMD:C_0603_1608Metric","2","crystal load"
"D1,D4","green","LED_SMD:LED_0603_1608Metric","2","power LED,status LED 1"
"D2,D3","BAV99","Package_TO_SOT_SMD:SOT-23","2","input clamp to analog rails"
"D5","yellow","LED_SMD:LED_0603_1608Metric","1","status LED 2"
"F1","0.5A hold","Fuse:Fuse_1206_3216Metric","1","resettable fuse, 500 mA hold"
"FB1,FB2","BLM18PG221","Inductor_SMD:L_0603_1608Metric","2","analog +5 V filter,analog -5 V filter"
"H1-H4","M3","MountingHole:MountingHole_3.2mm_M3","4","mounting hole"
"J1","USB-B","Connector_USB:USB_B_OST_USB-B1HSxx_Horizontal","1","USB 2.0 type-B receptacle"
"J2,J3","BNC","Connector_Coaxial:BNC_Amphenol_B6252HB-NPP3G-50_Horizontal","2","channel A input (scope-probe compatible),channel B input (scope-probe compatible)"
"J4","PROG","Connector_PinHeader_2.54mm:PinHeader_2x05_P2.54mm_Vertical","1","SPI flash programming header (iceprog-style)"
"L1","2.2u XFL4020-222","Inductor_SMD:L_Coilcraft_XxL4020","1","buck inductor"
"R1","1M","Resistor_SMD:R_0603_1608Metric","1","shield bleed"
"R2","453k","Resistor_SMD:R_0603_1608Metric","1","FB top: Vout = 0.6*(1+453k/100k) = 3.32 V"
"R3","100k","Resistor_SMD:R_0603_1608Metric","1","FB bottom"
"R4,R12,R32,R57,R58","1k","Resistor_SMD:R_0603_1608Metric","5","Resistor,buffer input isolation"
"R10,R30","909k 0.1%","Resistor_SMD:R_1206_3216Metric","2","attenuator top"
"R11,R31","100k 0.1%","Resistor_SMD:R_0603_1608Metric","2","attenuator bottom"
"R13,R16,R33,R36","806","Resistor_SMD:R_0603_1608Metric","4","MFB R1 (reference leg),MFB R1 (signal leg)"
"R14,R17,R34,R37","768","Resistor_SMD:R_0603_1608Metric","4","MFB R2 (reference leg),MFB R2 (signal leg)"
"R15,R18,R35,R38","147","Resistor_SMD:R_0603_1608Metric","4","MFB R3 (reference leg),MFB R3 (signal leg)"
"R19,R20,R39,R40","49.9","Resistor_SMD:R_0603_1608Metric","4","ADC drive / RC pole"
"R50,R51","100","Resistor_SMD:R_0603_1608Metric","2","PLL supply filter"
"R52-R54,R61,R63-R65,R71,R72","10k","Resistor_SMD:R_0603_1608Metric","9","ADC held in shutdown until FPGA enables it,Resistor,SS_B high at reset -> SPI master boot"
"R55,R73,R74","33","Resistor_SMD:R_0603_1608Metric","3","ADC clock series term,FPGA copy of sample clock,Resistor"
"R56","22","Resistor_SMD:R_0603_1608Metric","1","SDRAM clock series term"
"R60","12k 1%","Resistor_SMD:R_0603_1608Metric","1","FT232H PHY reference"
"R62","2.2k","Resistor_SMD:R_0603_1608Metric","1","EEPROM DO -> EEDATA"
"R70","20k","Resistor_SMD:R_0603_1608Metric","1","MODE = VDD/3: offset binary, DCS on"
"U1","USBLC6-2SC6","Package_TO_SOT_SMD:SOT-23-6","1","USB ESD protection"
"U2","TLV62569DBV","Package_TO_SOT_SMD:SOT-23-5","1","5V->3.3V 2 A buck"
"U3","TLV73312PDBV","Package_TO_SOT_SMD:SOT-23-5","1","FPGA core 1.2 V LDO"
"U4","LP5907MFX-3.3","Package_TO_SOT_SMD:SOT-23-5","1","low-noise ADC supply"
"U5","TPS60403DBV","Package_TO_SOT_SMD:SOT-23-5","1","inverting charge pump, 60 mA"
"U10,U11","OPA810IDBVR","Package_TO_SOT_SMD:SOT-23-5","2","FET-input unity-gain buffer"
"U12,U13","THS4521IDGK","Package_SO:VSSOP-8_3x3mm_P0.65mm","2","fully-differential ADC driver / 2-pole MFB"
"U20","LTC2290CUP","Package_DFN_QFN:QFN-64-1EP_9x9mm_P0.5mm_EP7.15x7.15mm","1","dual 12-bit 10 Msps ADC"
"U30","ICE40HX4K-TQ144","Package_QFP:TQFP-144_20x20mm_P0.5mm","1","FPGA: capture, SDRAM, USB FIFO"
"U31","W25Q32JVSSIQ","Package_SO:SOIC-8_5.3x5.3mm_P1.27mm","1","FPGA configuration flash (32 Mbit)"
"U40","MT48LC16M16A2P-6A","Package_SO:TSOP-II-54_22.2x10.16mm_P0.8mm","1","256 Mbit SDR SDRAM capture buffer"
"U50","FT232HL","Package_QFP:LQFP-48_7x7mm_P0.5mm","1","USB 2.0 HS to sync FIFO bridge"
"U51","93LC56BT-I/OT","Package_TO_SOT_SMD:SOT-23-6","1","FT232H config EEPROM (sets 245 sync FIFO mode)"
"X1","ASE-10.000MHZ","Oscillator:Oscillator_SMD_Abracon_ASE-4Pin_3.2x2.5mm","1","10 MHz sample clock (dedicated, low jitter)"
"X2","ASE-50.000MHZ","Oscillator:Oscillator_SMD_Abracon_ASE-4Pin_3.2x2.5mm","1","50 MHz system clock"
"Y1","12MHz 10pF","Crystal:Crystal_SMD_3225-4Pin_3.2x2.5mm","1","FT232H crystal"

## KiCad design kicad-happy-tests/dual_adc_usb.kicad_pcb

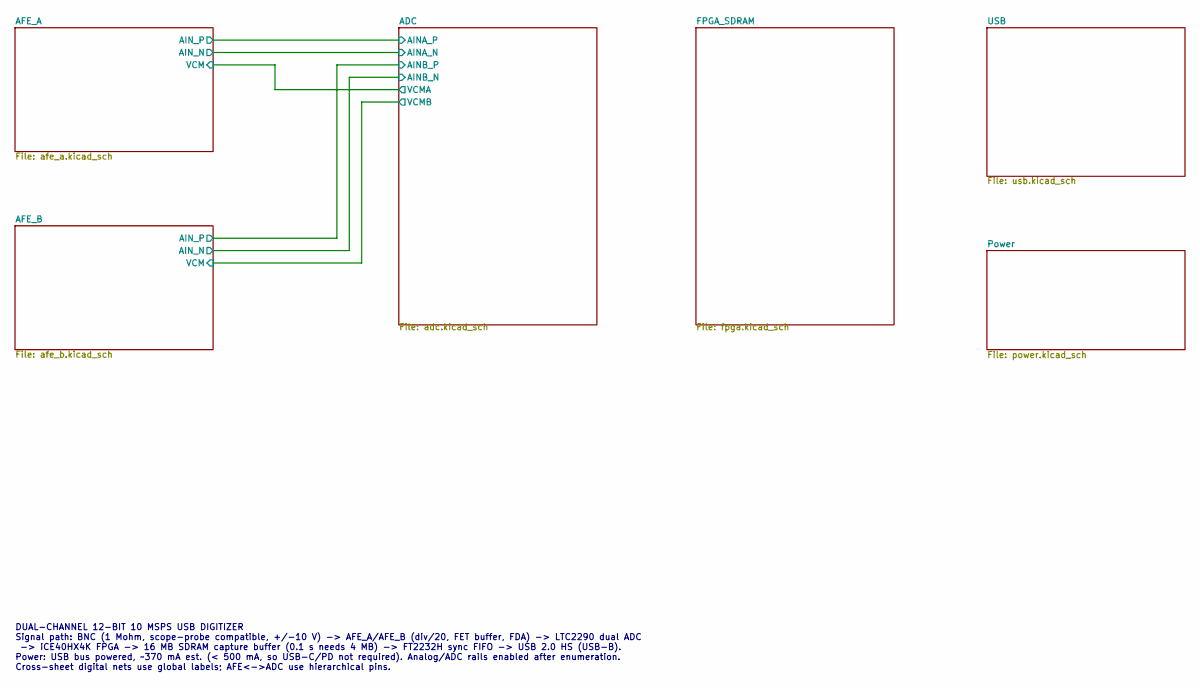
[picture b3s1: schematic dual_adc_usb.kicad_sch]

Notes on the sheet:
DUAL-CHANNEL 12-BIT 10 MSPS USB DIGITIZER Signal path: BNC (1 Mohm, scope-probe compatible, +/-10 V) -> AFE_A/AFE_B (div/20, FET buffer, FDA) -> LTC2290 dual ADC -> iCE40HX4K FPGA -> 16 MB SDRAM capture buffer (0.1 s needs 4 MB) -> FT2232H sync FIFO -> USB 2.0 HS (USB-B). Power: USB bus powered, ~3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
